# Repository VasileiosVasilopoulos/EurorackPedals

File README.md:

## Eurorack Pedals

Collection of Guitar and Bass Pedal pcbs designed to fit the [Eurorack](https://en.wikipedia.org/wiki/Eurorack) format.
designed with the free version of [Eagle](https://www.autodesk.com/products/eagle/free-download?plc=F360&term=1-YEAR&support=ADVANCED&quantity=1).

The Eurorack specifications followed are:

- Height 3U 
- Width>10HP.  

The width specification ensures that there is enough space between the footswitch of subsequent modules.

The power does not follow the Eurorack format since most analog pedals need a 9V input.

To connect a chain of pedals to classic Eurorack modules, the signal needs to be amplified.

For more information contact me at:  
email: vvasilopoulos99@gmail.com  
linkedin: www.linkedin.com/in/vasileios-vasilopoulos  

### Licence

The designs are free to use non-commercially.

I would not recommend using commercially since 
copyrights may apply to the schematics / fonts etc.

### List of pedals

#### Utility
- [3PDT](3PDT_Breakout) Foot Switch Breakout Board
- [Groupie](Groupie): Bypass a chain of effects
- TODO Amplifier/Attenuator to connect guitar to eurorack and the other way around. 1U Tile
- TODO PSU - 12V to multiple isolated 9V
- TODO In/Out - 6.35mm to 3.5mm Input, 3.5mm to 6.35mm Output
 
#### Fuzz 
- [Randy's Gut](Randys_Gut) (Similar to EQD Dirt Transmitter)
- [Zeus](Zeus) (Similar to EQD Blach Ash)

#### Octaver
- [Poseidon](Poseidon) (Similar to EQD Tentacle)

### Resources 

I'd like to thank all the people offering to the DIY community and link some resources that helped me get familiar with designing pcb's.

Jeremy Blum's [youtube channel](https://www.youtube.com/user/sciguy14) has some good tutorials for EAGLE basics.

Effect's Layout [blog](http://effectslayouts.blogspot.com/) / [youtube](https://www.youtube.com/channel/UCuCJhqsyaGveg0PjLbAGcdQ) has a big variety of pedal designs for perfboards / pcb etching. Also a nice tutorial series for EAGLE and a pack of EAGLE libraries with focus to pcb design for pedals. 

[MadBeanPedals](https://www.madbeanpedals.com/) has some designs and tutorials for homemade pcb etching. He also has a very helpful EAGLE library.

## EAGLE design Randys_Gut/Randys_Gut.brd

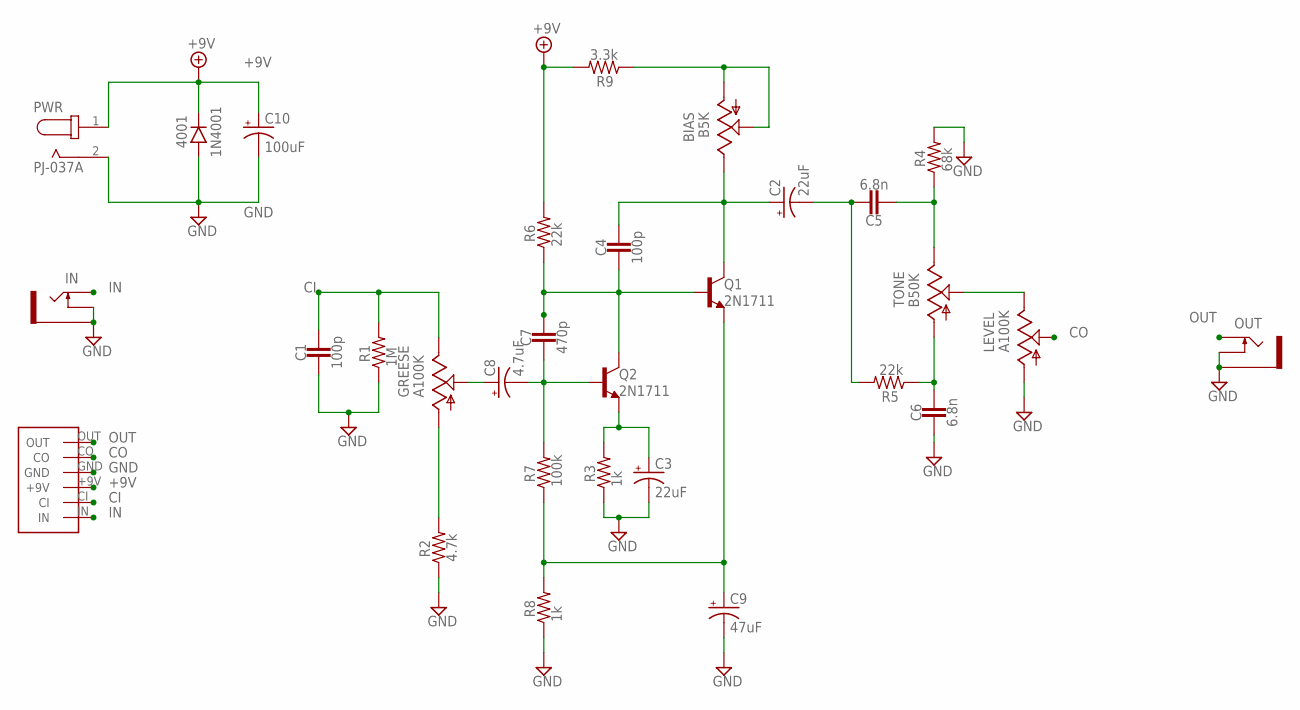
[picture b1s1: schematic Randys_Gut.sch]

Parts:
4001: 1N4001; DO41-3
BIAS: B5K; 9MM_SNAP-IN_POT
C1, C4: 100p; 0.2".SML
C2, C3: 22uF; 050_020_1
C5, C6: 6.8n; 0.2".SML
C7: 470p; 0.2".SML
C8: 4.7uF; 050_020_1
C9: 47uF; 063_025
C10: 100uF; 063_025
GREESE: A100K; 9MM_SNAP-IN_POT
IN: THONKICONNNEW; WQP-PJ301M-12_JACK
LEVEL: A100K; 9MM_SNAP-IN_POT
OUT: THONKICONNNEW; WQP-PJ301M-12_JACK
PWR: PJ-037A; CUI_PJ-037A
Q1, Q2: 2N1711; TO18
R1: 1M; R0207/3
R2: 4.7k; R0207/3
R3, R8: 1k; R0207/3
R4: 68k; R0207/3
R5, R6: 22k; R0207/3
R7: 100k; R0207/3
R9: 3.3k; R0207/3
TONE: B50K; 9MM_SNAP-IN_POT
U$2: HEADERS6

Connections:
+9V: 4001.C, C10.+, PWR.1, R6.2, R9.2, U$2.+9V
C3: C7.2, C8.-, Q2.2 (B), R7.2
CI: C1.1, GREESE.3 (E), R1.2, U$2.CI
CO: LEVEL.2 (S), U$2.CO
GND: 4001.A, C1.2, C3.-, C6.2, C9.-, C10.-, IN.P$2_SWITCH (SWITCH), IN.P$3_SLEEVE (SLEEVE), LEVEL.1 (A), OUT.P$2_SWITCH (SWITCH), OUT.P$3_SLEEVE (SLEEVE), PWR.2, R1.1, R2.1, R3.1, R4.2, R8.1, U$2.GND
IN: IN.P$1_TIP (TIP), U$2.IN
unnamed: GREESE.1 (A), R2.2
unnamed: C8.+, GREESE.2 (S)
unnamed: C9.+, Q1.1 (E), R7.1, R8.2
unnamed: C4.2, C7.1, Q1.2 (B), Q2.3 (C), R6.1
unnamed: C3.+, Q2.1 (E), R3.2
unnamed: BIAS.3 (E), C2.+, C4.1, Q1.3 (C)
unnamed: C2.-, C5.1, R5.2
unnamed: BIAS.1 (A), BIAS.2 (S), R9.1
unnamed: C5.2, R4.1, TONE.3 (E)
unnamed: C6.1, R5.1, TONE.1 (A)
unnamed: LEVEL.3 (E), TONE.2 (S)
OUT: OUT.P$1_TIP (TIP), U$2.OUT

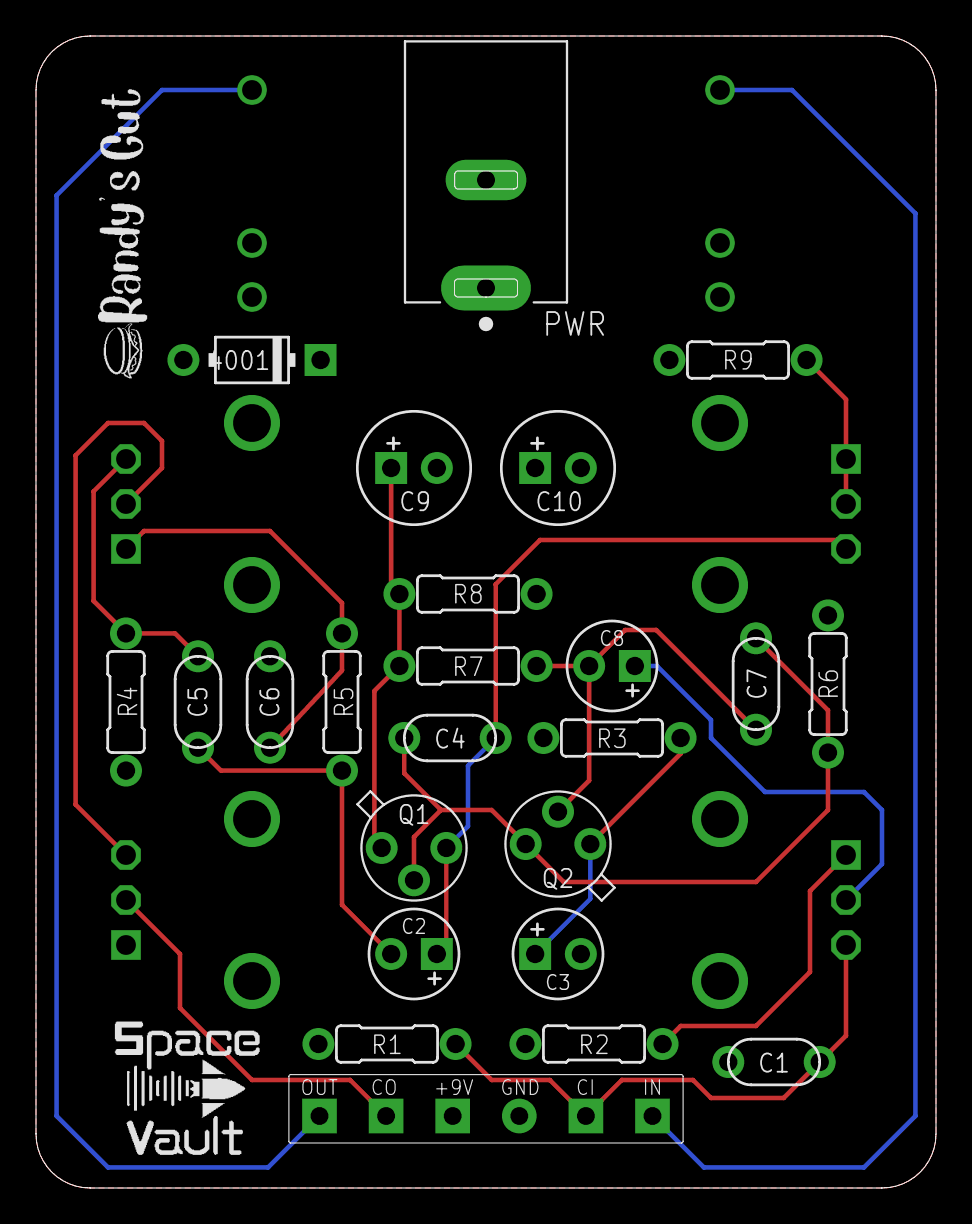
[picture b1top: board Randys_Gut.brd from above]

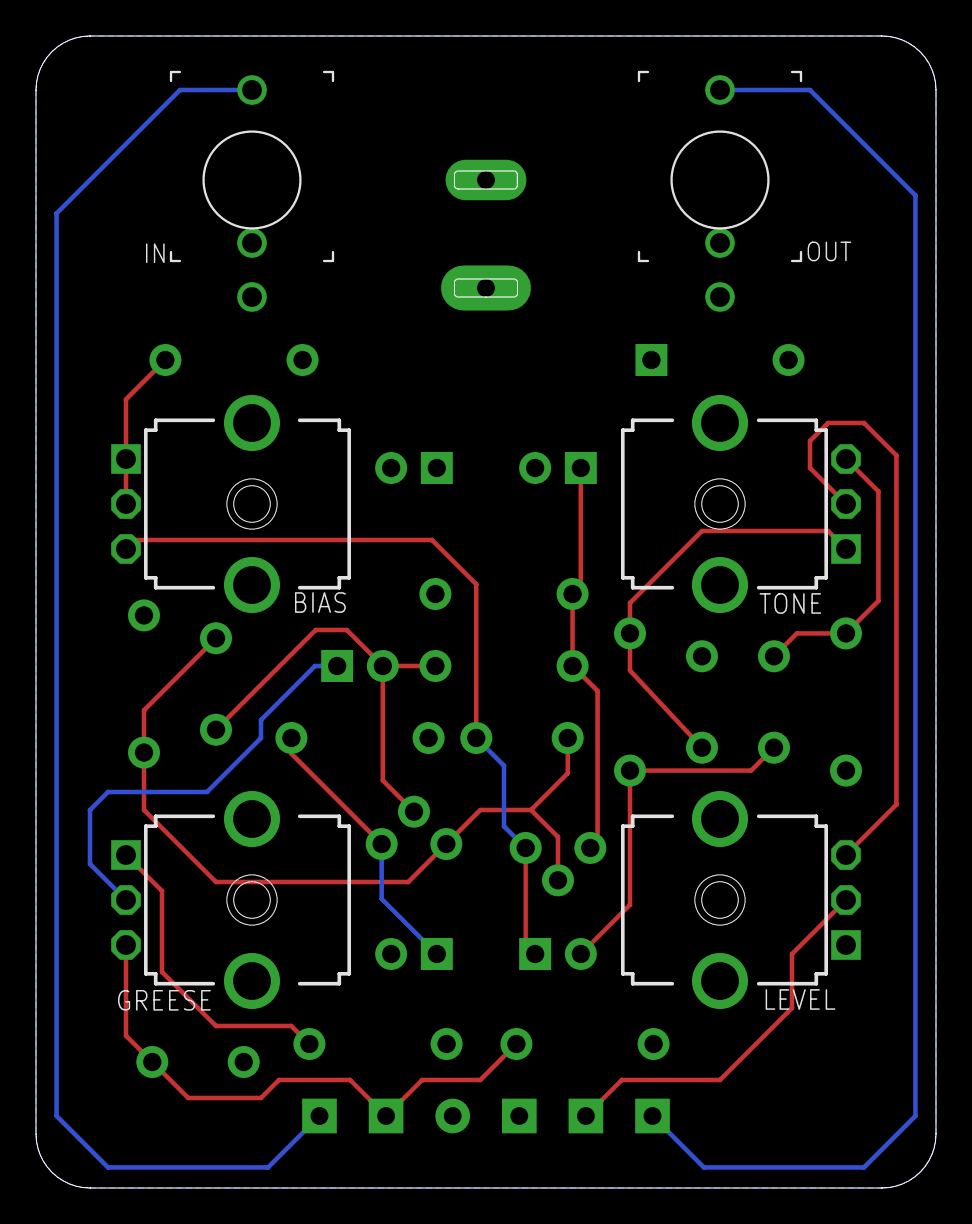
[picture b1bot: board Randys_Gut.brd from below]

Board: 2 copper layers, 50.0 x 64.0 mm, 31 parts (6 on the bottom side), 18 nets.

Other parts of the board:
U$1: PANEL_12HP_NO_SWITCH

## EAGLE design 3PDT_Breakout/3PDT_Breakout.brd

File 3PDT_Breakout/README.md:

## 3PDT Breakout Board

3PDT Breakout board with current limiting resistor and spot for 3mm LED.

3PDT Switches have small variations in dimensions so make sure to check your switch documentation and modify the footprint if needed.

### Board Preview: 

Front             |  Back
:-------------------------:|:-------------------------:
  |

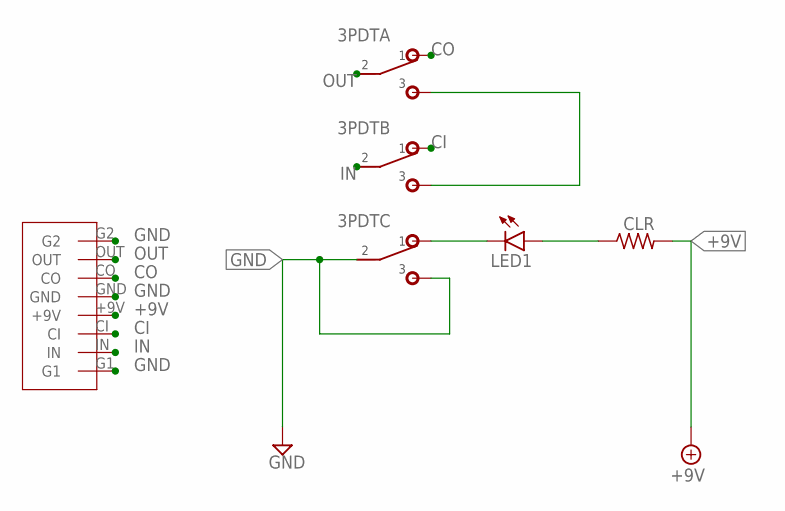
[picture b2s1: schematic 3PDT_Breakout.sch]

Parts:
3PDT: 3PDT
CLR: RESISTORS.3B; R0207/3
LED1: LED3MM
U$1: HEADERS8

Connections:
+9V: CLR.2, U$1.+9V
CI: 3PDT.B1 (1), U$1.CI
CO: 3PDT.A1 (1), U$1.CO
GND: 3PDT.C2 (2), 3PDT.C3 (3), U$1.G1, U$1.G2, U$1.GND
IN: 3PDT.B2 (2), U$1.IN
unnamed: 3PDT.C1 (1), LED1.K (C)
unnamed: CLR.1, LED1.A
unnamed: 3PDT.A3 (3), 3PDT.B3 (3)
OUT: 3PDT.A2 (2), U$1.OUT

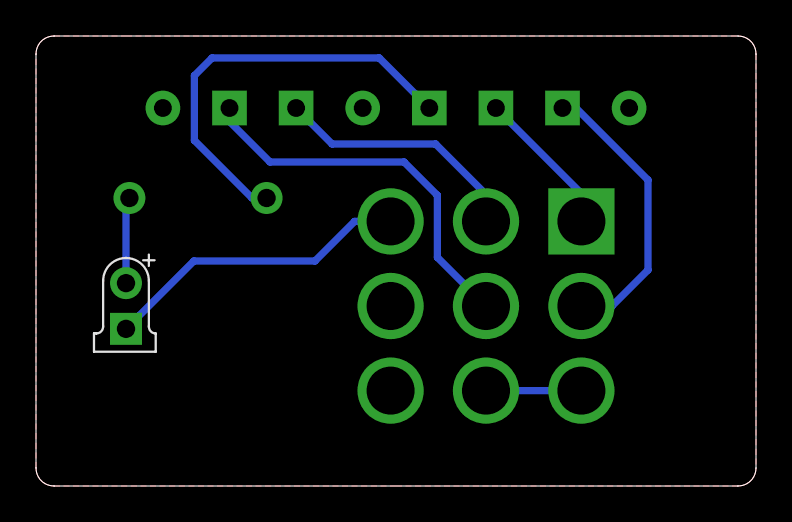
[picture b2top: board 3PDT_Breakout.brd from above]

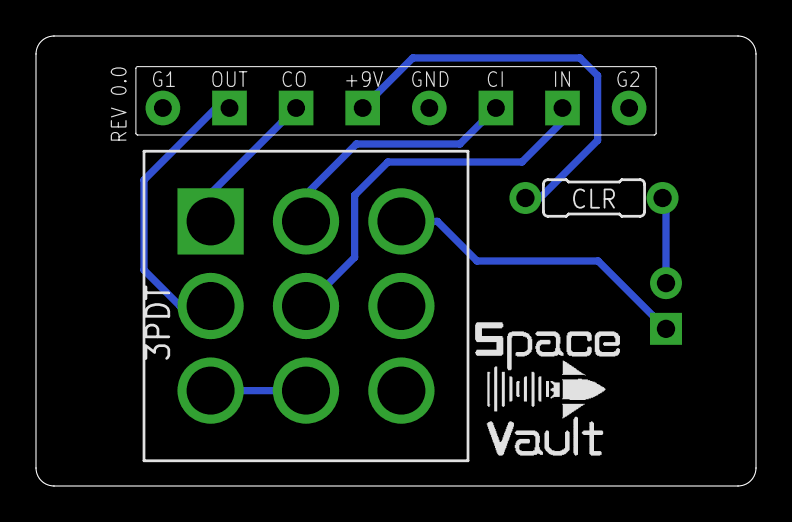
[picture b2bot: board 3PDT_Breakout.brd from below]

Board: 2 copper layers, 40.0 x 25.0 mm, 4 parts (3 on the bottom side), 9 nets.

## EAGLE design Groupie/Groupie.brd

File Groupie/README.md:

## Groupie

Utility  

Designed by Vasilopoulos Vasileios  
email : vvasilopoulos99@gmail.com  

Utility module to add True Bypass to a series of other modules.  

A100K Potentiometer controls the overall volume of the chain.  

Best combined with the - [3PDT  Breakout Board](../3PDT_Breakout)
### Board Preview: 

Front             |  Back
:-------------------------:|:-------------------------:
  |

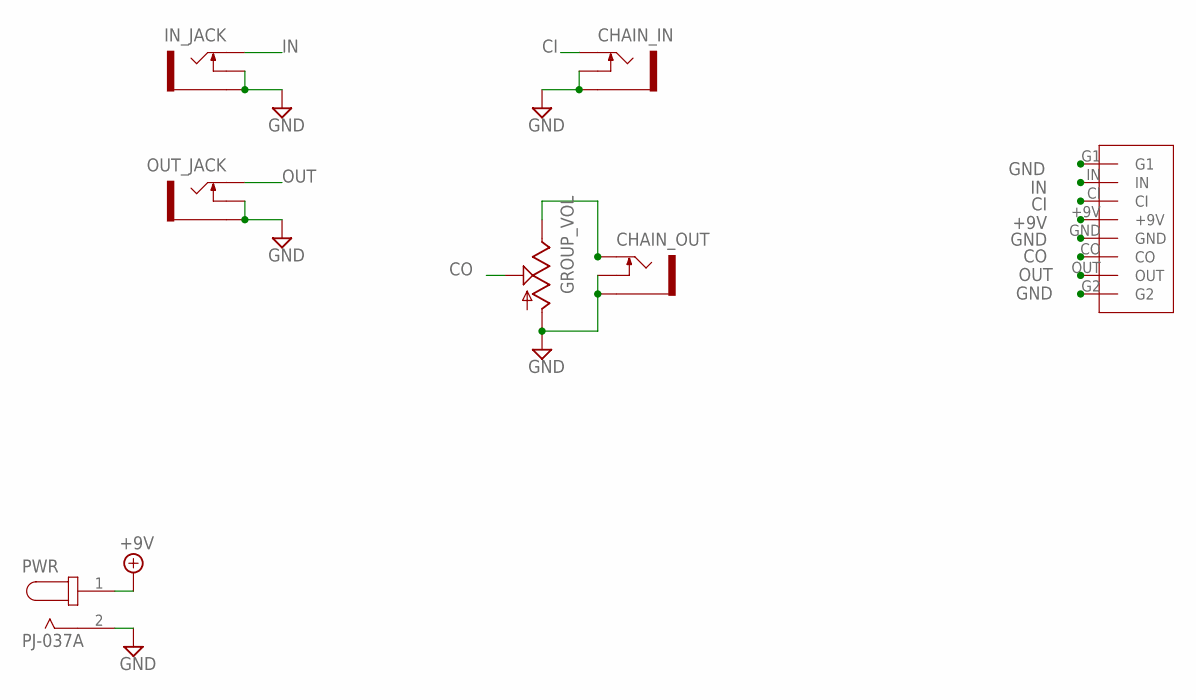
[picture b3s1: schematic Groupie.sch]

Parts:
CHAIN_IN: THONKICONNNEW; WQP-PJ301M-12_JACK
CHAIN_OUT: THONKICONNNEW; WQP-PJ301M-12_JACK
GROUP_VOL: 9MM_SNAP-IN_POT_; 9MM_SNAP-IN_POT
HEADERS: HEADERS8
IN_JACK: THONKICONNNEW; WQP-PJ301M-12_JACK
OUT_JACK: THONKICONNNEW; WQP-PJ301M-12_JACK
PWR: PJ-037A; CUI_PJ-037A

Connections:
+9V: HEADERS.+9V, PWR.1
CI: CHAIN_IN.P$1_TIP (TIP), HEADERS.CI
CO: GROUP_VOL.2 (S), HEADERS.CO
GND: CHAIN_IN.P$2_SWITCH (SWITCH), CHAIN_IN.P$3_SLEEVE (SLEEVE), CHAIN_OUT.P$2_SWITCH (SWITCH), CHAIN_OUT.P$3_SLEEVE (SLEEVE), GROUP_VOL.1 (A), HEADERS.G1, HEADERS.G2, HEADERS.GND, IN_JACK.P$2_SWITCH (SWITCH), IN_JACK.P$3_SLEEVE (SLEEVE), OUT_JACK.P$2_SWITCH (SWITCH), OUT_JACK.P$3_SLEEVE (SLEEVE), PWR.2
IN: HEADERS.IN, IN_JACK.P$1_TIP (TIP)
unnamed: CHAIN_OUT.P$1_TIP (TIP), GROUP_VOL.3 (E)
OUT: HEADERS.OUT, OUT_JACK.P$1_TIP (TIP)

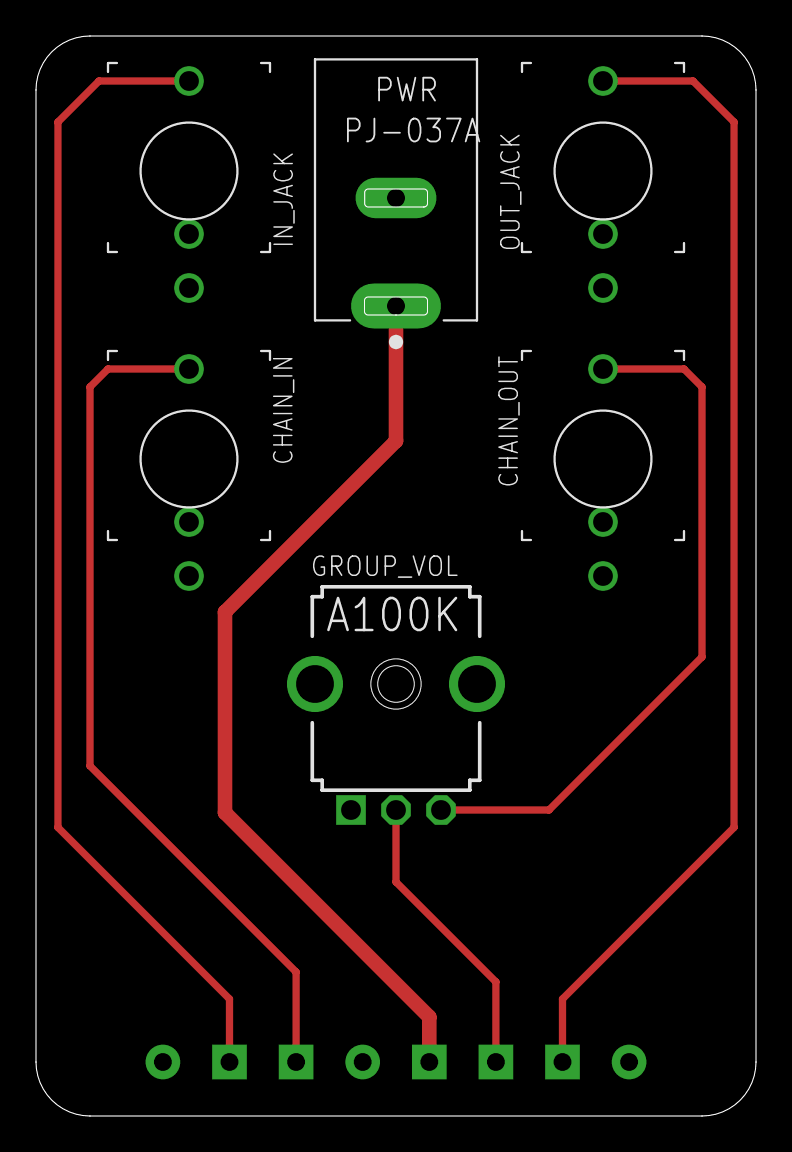
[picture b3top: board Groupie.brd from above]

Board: 2 copper layers, 40.0 x 60.0 mm, 7 parts (1 on the bottom side), 7 nets.

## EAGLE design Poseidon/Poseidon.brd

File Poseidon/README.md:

## Poseidon

Octaver

Schematic based on the EQD Tentacle.

### Board Preview: 

<!-- ##### Front -->

<!--  -->
<!--  

##### Back

 -->

<!--   |   -->

Front             |  Back
:-------------------------:|:-------------------------:
  |

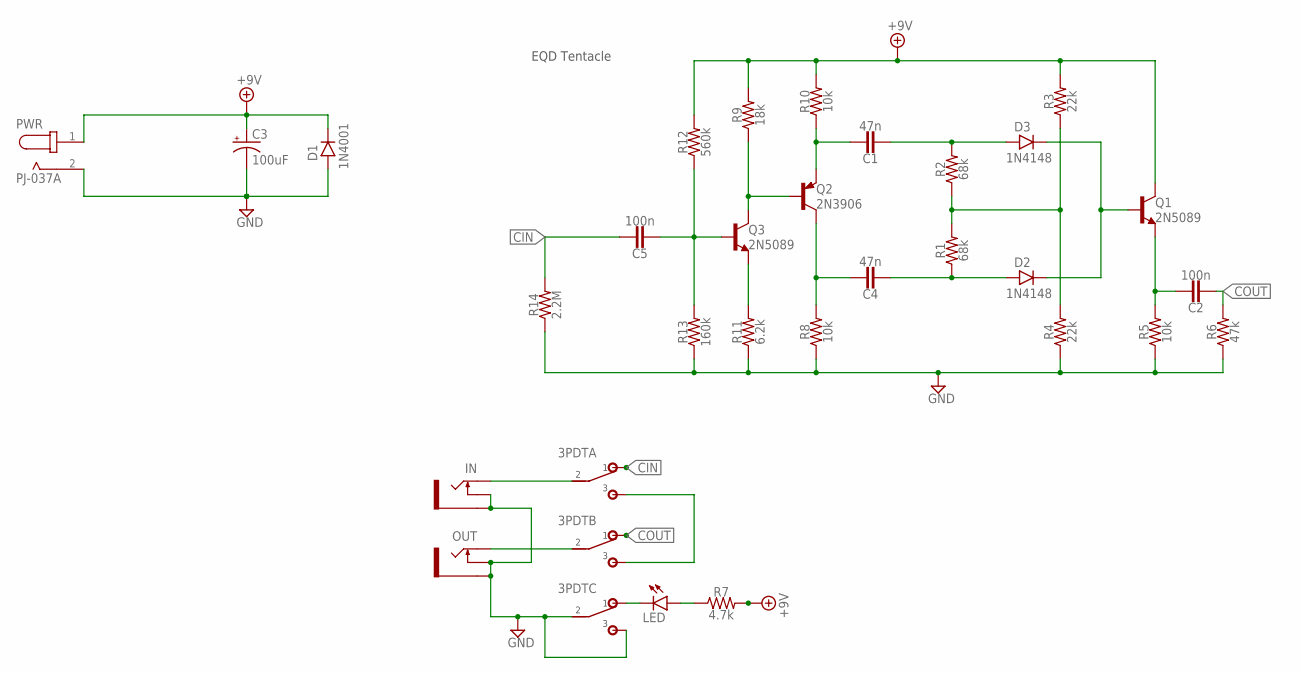
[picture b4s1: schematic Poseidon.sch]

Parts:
3PDT: 3PDT
C1, C4: 47n; 0.2".SML
C2, C5: 100n; 0.2".SML
C3: 100uF; 063_025
D1: 1N4001; DO41-3
D2, D3: 1N4148; DO35-3
IN: NV-PJ3410_MONO; NV-PJ3410_SOCKET_MONO
LED: LED3MM
OUT: NV-PJ3410_MONO; NV-PJ3410_SOCKET_MONO
PWR: PJ-037A; CUI_PJ-037A
Q1, Q3: 2N5089; TO92
Q2: 2N3906; TO92
R1, R2: 68k; 0.3".B
R3, R4: 22k; 0.3".B
R5, R8, R10: 10k; 0.3".B
R6: 47k; 0.3".B
R7: 4.7k; 0.3".B
R9: 18k; 0.3".B
R11: 6.2k; 0.3".B
R12: 560k; 0.3".B
R13: 160k; 0.3".B
R14: 2.2M; 0.3".B

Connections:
+9V: C3.+, D1.C, PWR.1, Q1.1 (C), R3.2, R7.2, R9.2, R10.2, R12.2
CIN: 3PDT.A1 (1), C5.1, R14.2
COUT: 3PDT.B1 (1), C2.2, R6.2
GND: 3PDT.C2 (2), 3PDT.C3 (3), C3.-, D1.A, IN.GND (SLEEVE), IN.SWITCH, OUT.GND (SLEEVE), OUT.SWITCH, PWR.2, R4.1, R5.1, R6.1, R8.1, R11.1, R13.1, R14.1
unnamed: 3PDT.A3 (3), 3PDT.B3 (3)
unnamed: C5.2, Q3.2 (B), R12.1, R13.2
unnamed: 3PDT.C1 (1), LED.K (C)
unnamed: Q3.3 (E), R11.2
unnamed: LED.A, R7.1
unnamed: Q2.2 (B), Q3.1 (C), R9.1
unnamed: C1.1, Q2.3 (E), R10.1
unnamed: 3PDT.A2 (2), IN.LEFT (TIP)
unnamed: C4.1, Q2.1 (C), R8.2
unnamed: C4.2, D2.A, R1.1
unnamed: R1.2, R2.1, R3.1, R4.2
unnamed: C1.2, D3.A, R2.2
unnamed: 3PDT.B2 (2), OUT.LEFT (TIP)
unnamed: D2.C, D3.C, Q1.2 (B)
unnamed: C2.1, Q1.3 (E), R5.2

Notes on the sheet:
EQD Tentacle

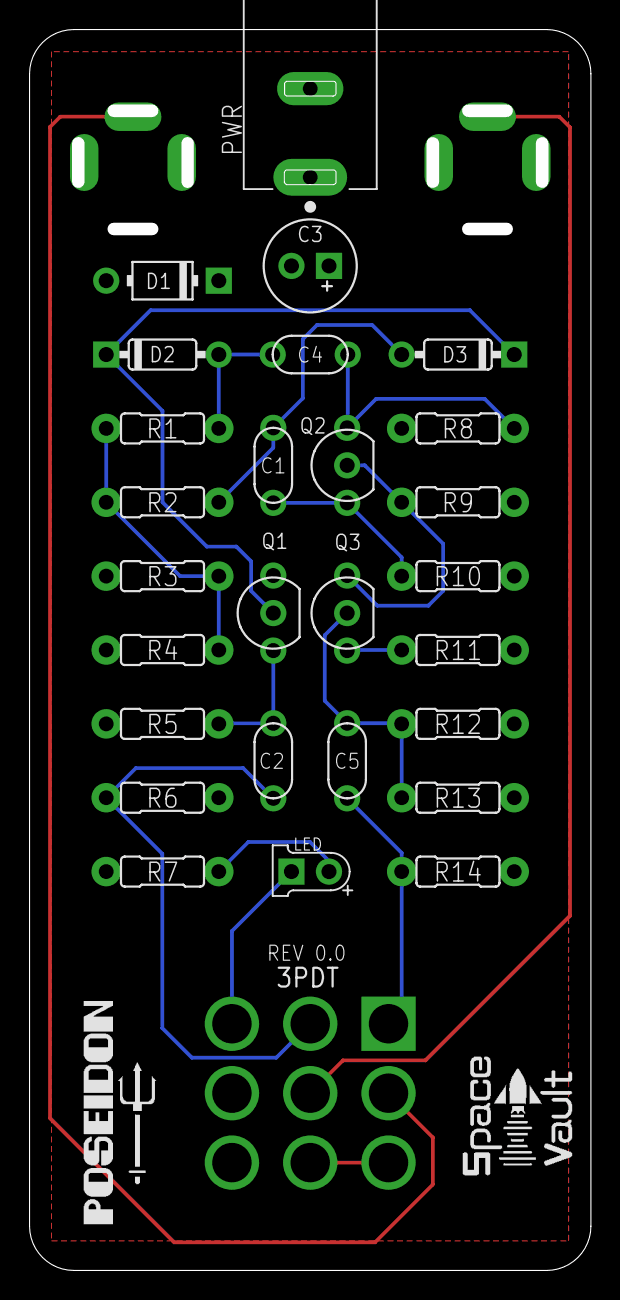
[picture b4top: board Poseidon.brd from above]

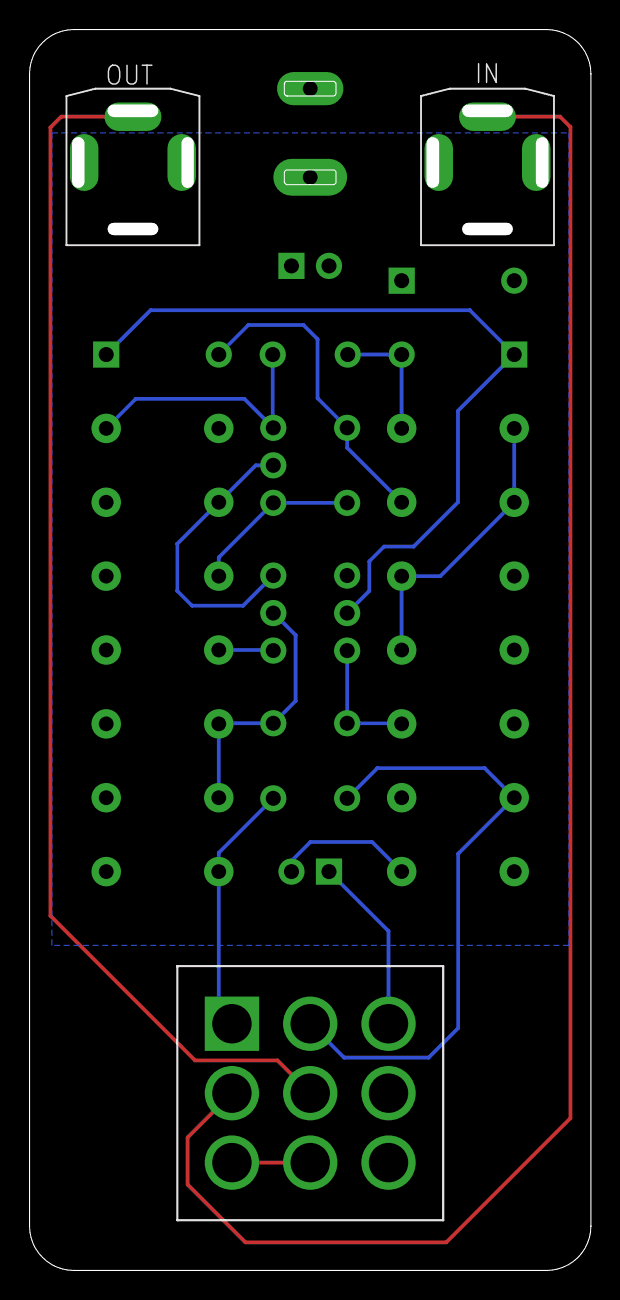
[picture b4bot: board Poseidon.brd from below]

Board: 2 copper layers, 37.2 x 83.2 mm, 30 parts (3 on the bottom side), 19 nets.

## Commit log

2020-12-01 Adding Schematics
2020-12-01 Adding effects
2020-12-01 New board for Poseidon
2020-12-02 Added images
2020-12-02 Image size
2020-12-03 Added boards
2020-12-03 Added Readme
2020-12-03 Changes to README
2021-05-27 Added gitignore

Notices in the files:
parts and their libraries:
SparkFun-Aesthetics: Licensing: Creative Commons ShareAlike 4.0 International - https://creativecommons.org/licenses/by-sa/4.0
